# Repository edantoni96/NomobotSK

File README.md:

# NomobotSK

========== PCB DESIGN FOR NOMOBOT SK ==========

NomobotSK is a educational robot for kids to learn programming and robotics.

## TOP VIEW

## BOTTOM VIEW

## SCHEMATIC

[embed](https://github.com/edantoni96/NomobotSK/blob/main/docs/schematic.pdf)

## TESTER

To test the device you can use the under tester/TEST.ino

\***\*KONFIGURASI PIN\*\***

D1; Trig / Servo R
D2; Tombol 2
D3; Tombol 3
D4; DIR2 (-)
D5; DIR2 (+)
D6; DIR1 (-)
D7; DIR1 (+)
D8; LED / Garis L
D0; BUZZ / Garis R

Catatan: Simbol / berarti setiap fungsi perlu diuji atau digunakan secara terpisah.

\***\*Perintah PENGUJIAN\*\***

1. TEST_LED
2. TEST_BUZ
3. TEST_BUTTON
4. TEST_M1
5. TEST_M2
6. TEST_ULRA
7. TEST_LINE

\***\*Instruksi Uji\*\***

1. Buka Test.ino dengan Arduino.
2. compile Test.ino.
3. Hubungkan NodeMCU Anda ke komputer menggunakan kabel USB.
4. Pilih board dan port yang sesuai di Arduino IDE.
5. Unggah kode yang telah dikompilasi ke NodeMCU dengan mengklik tombol "Unggah".
6. Setelah pengunggahan selesai, buka Serial Monitor di Arduino IDE.
7. TEST_LED
   - Nyalakan pin LED
   - Ketik "TEST_LED" di Serial Monitor dan tekan Enter.
   - Pastikan bahwa LED yang terhubung ke pin D8 (Garis L) menyala.
8. TEST_BUZ
   - Nyalakan pin Buzz
   - Ketik "TEST_BUZ" di Serial Monitor dan tekan Enter.
   - Konfirmasikan bahwa buzzer yang terhubung ke pin D0 (Garis R) menghasilkan suara.
9. TEST_BUTTON
   - Nyalakan BTA dan BTB
   - Ketik "TEST_BUTTON" di Serial Monitor dan tekan Enter.
   - Tekan Tombol 2 (terhubung ke pin D2) dan Tombol 3 (terhubung ke pin D3) satu per satu.
   - Amati di Serial Monitor bahwa tekanan tombol yang sesuai terdeteksi.
10. TEST_M1
    - Nyalakan pin M1+ dan M1-
    - Ketik "TEST_M1" di Serial Monitor dan tekan Enter.
    - Pastikan bahwa motor (M1) merespons sesuai dengan sinyal DIR1 (-) dan DIR1 (+) pada pin D6 dan D7.
11. TEST_M2
    - Nyalakan pin M2+ dan M2-
    - Ketik "TEST_M2" di Serial Monitor dan tekan Enter.
    - Pastikan bahwa motor (M2) merespons sesuai dengan sinyal DIR2 (-) dan DIR2 (+) pada pin D4 dan D5.
12. TEST_ULRA
    - Nyalakan pin Echo dan Trig
    - Ketik "TEST_ULRA" di Serial Monitor dan tekan Enter.
    - Jika sensor ultrasonik terhubung, periksa Serial Monitor untuk pembacaan jarak.
13. TEST_LINE
    - Nyalakan pin Garis
    - Ketik "TEST_LINE" di Serial Monitor dan tekan Enter.
    - Amati perilaku sensor garis yang terhubung ke pin D8 (Garis L) dan D0 (Garis R).
    - Pastikan pembacaan sensor tercermin di Serial Monitor.

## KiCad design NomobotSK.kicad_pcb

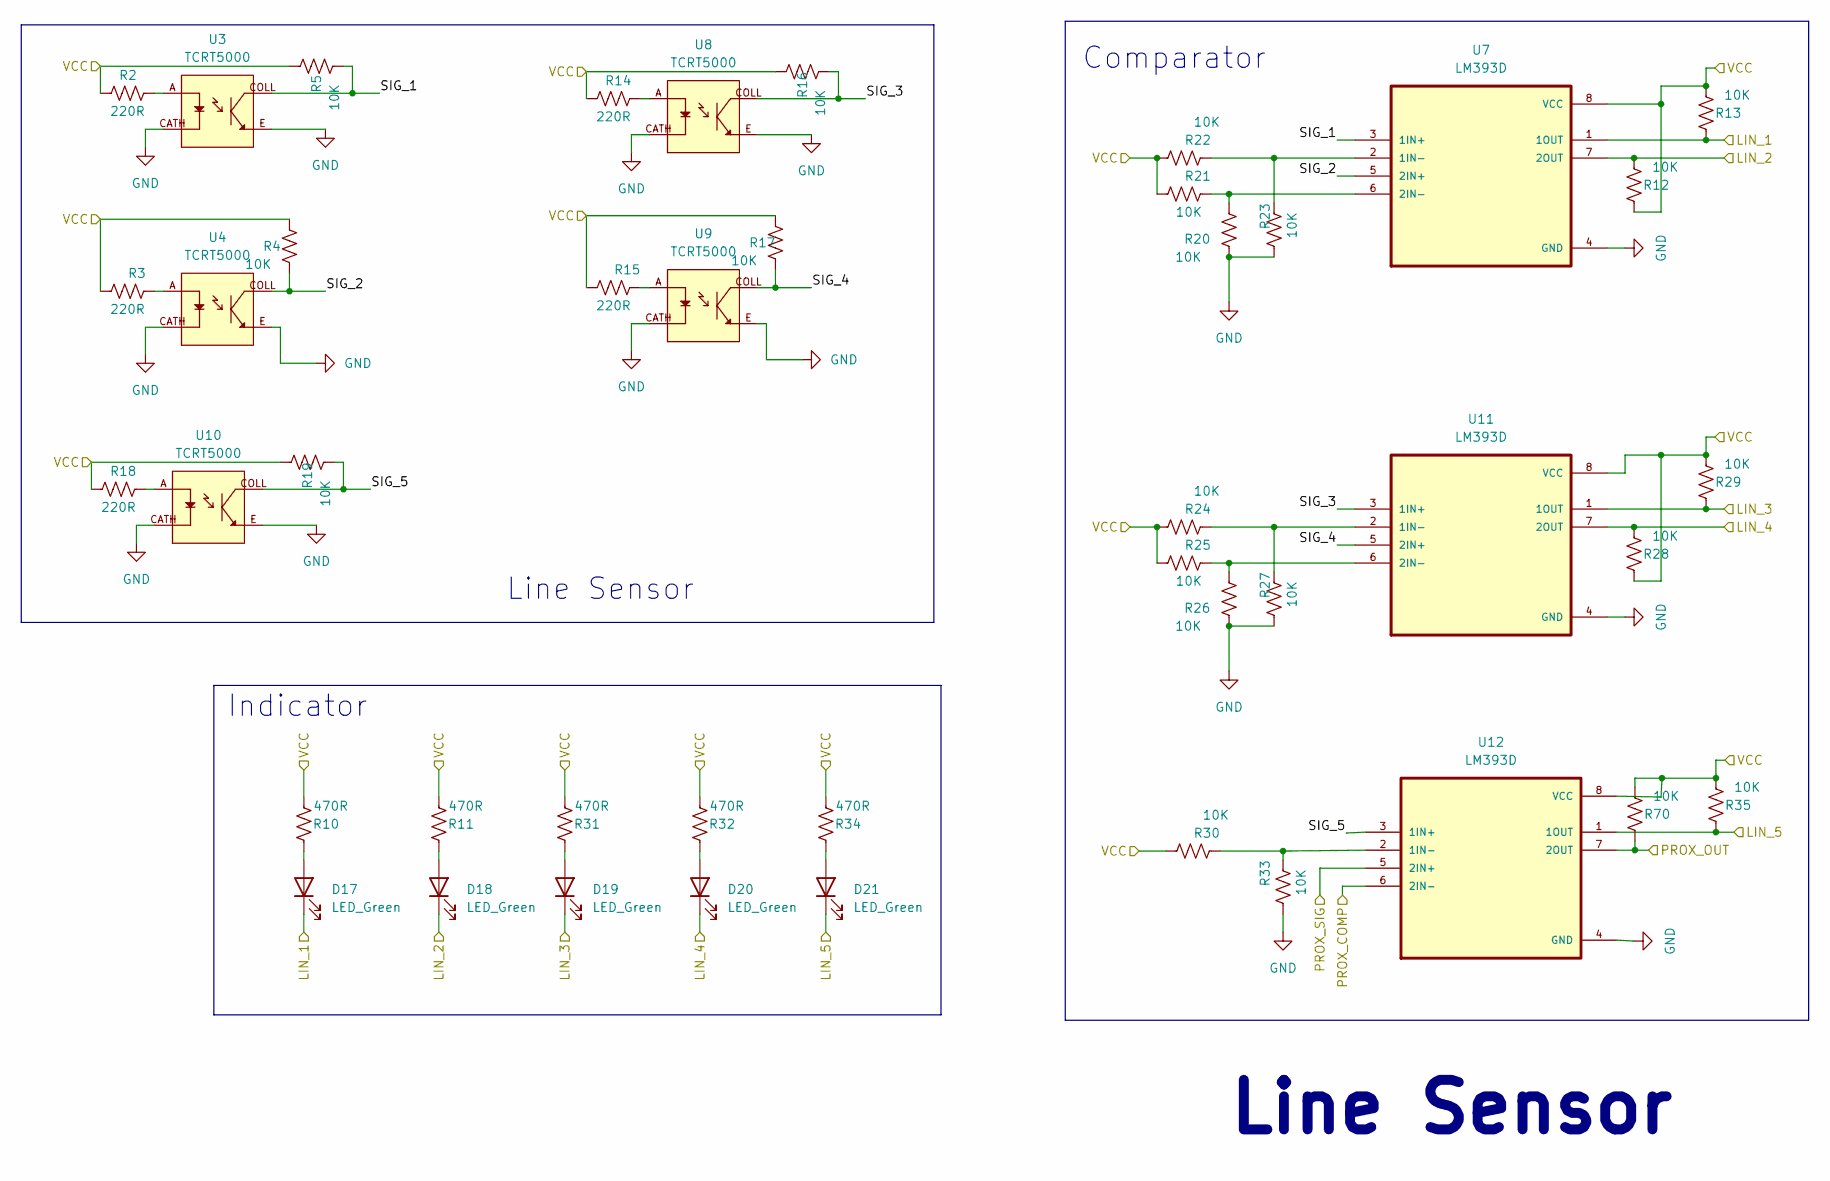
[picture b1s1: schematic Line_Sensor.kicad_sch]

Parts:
D17, D18, D19, D20, D21: LED_Green; LED_0805_2012Metric
R2, R3, R14, R15, R18: 220R; R_0805_2012Metric
R4, R5, R12, R13, R16, R17, R19, R20, R21, R22, R23, R24, R25, R26, R27, R28, R29, R30, R33, R35, R70: 10K; R_0805_2012Metric
R10, R11, R31, R32, R34: 470R; R_0805_2012Metric
U3, U4, U8, U9, U10: TCRT5000; OPTO_TCRT5000; PARTREV 1.7
U7, U11, U12: LM393D; SOIC127P599X175-8N

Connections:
/LINE SENSOR/LIN_1: D17.1 (K), R13.1, U7.1 (1OUT); also elsewhere on the board
/LINE SENSOR/LIN_2: D18.1 (K), R12.2, U7.7 (2OUT); also elsewhere on the board
/LINE SENSOR/LIN_3: D19.1 (K), R29.1, U11.1 (1OUT); also elsewhere on the board
/LINE SENSOR/LIN_4: D20.1 (K), R28.2, U11.7 (2OUT); also elsewhere on the board
/LINE SENSOR/LIN_5: D21.1 (K), R35.1, U12.1 (1OUT); also elsewhere on the board
/LINE SENSOR/PROX_COMP: U12.6 (2IN-); also elsewhere on the board
/LINE SENSOR/PROX_OUT: R70.1, U12.7 (2OUT); also elsewhere on the board
/LINE SENSOR/PROX_SIG: U12.5 (2IN+); also elsewhere on the board
/LINE SENSOR/SIG_1: R5.2, U3.COLL, U7.3 (1IN+)
/LINE SENSOR/SIG_2: R4.2, U4.COLL, U7.5 (2IN+)
/LINE SENSOR/SIG_3: R16.2, U8.COLL, U11.3 (1IN+)
/LINE SENSOR/SIG_4: R17.2, U9.COLL, U11.5 (2IN+)
/LINE SENSOR/SIG_5: R19.2, U10.COLL, U12.3 (1IN+)
/VDD: R2.2, R3.2, R4.1, R5.1, R10.2, R11.2, R12.1, R13.2, R14.2, R15.2, R16.1, R17.1, R18.2, R19.1, R21.2, R22.2, R24.2, R25.2, R28.1, R29.2, R30.2, R31.2, R32.2, R34.2, R35.2, R70.2, U7.8 (VCC), U11.8 (VCC), U12.8 (VCC); also elsewhere on the board
GND: R20.1, R23.2, R26.1, R27.2, R33.2, U3.CATH, U3.E, U4.CATH, U4.E, U7.4 (GND), U8.CATH, U8.E, U9.CATH, U9.E, U10.CATH, U10.E, U11.4 (GND), U12.4 (GND); also elsewhere on the board
unnamed: D17.2 (A), R10.1
unnamed: D18.2 (A), R11.1
unnamed: D19.2 (A), R31.1
unnamed: D20.2 (A), R32.1
unnamed: D21.2 (A), R34.1
unnamed: R2.1, U3.A
unnamed: R3.1, U4.A
unnamed: R14.1, U8.A
unnamed: R15.1, U9.A
unnamed: R18.1, U10.A
unnamed: R22.1, R23.1, U7.2 (1IN-)
unnamed: R20.2, R21.1, U7.6 (2IN-)
unnamed: R24.1, R27.1, U11.2 (1IN-)
unnamed: R25.1, R26.2, U11.6 (2IN-)
unnamed: R30.1, R33.1, U12.2 (1IN-)

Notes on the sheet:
Indicator
Line Sensor
Comparator

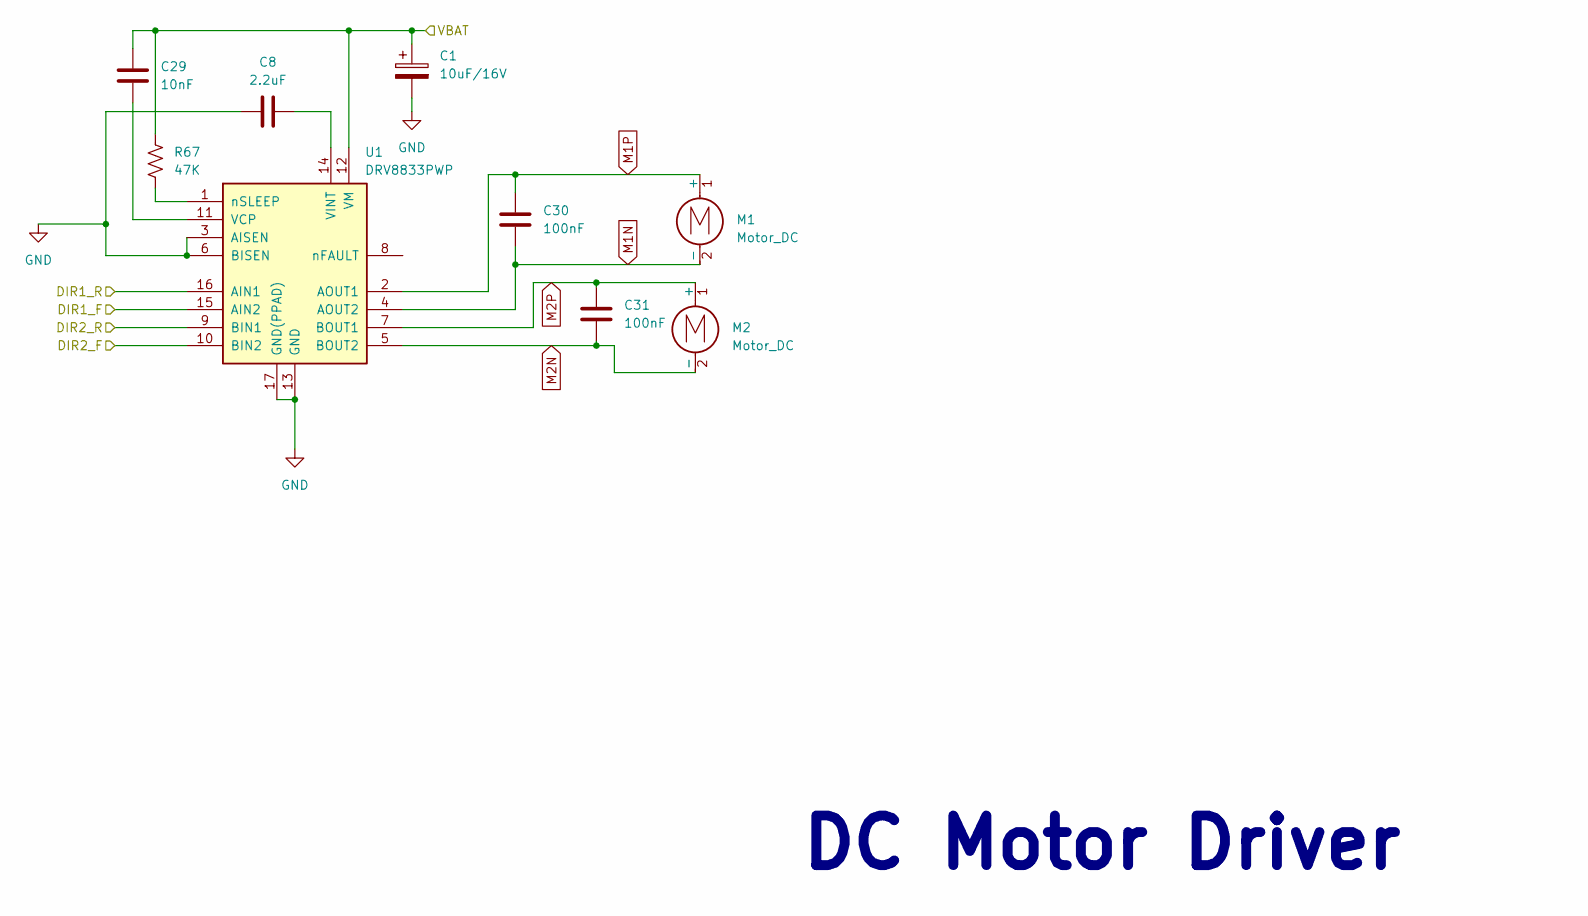
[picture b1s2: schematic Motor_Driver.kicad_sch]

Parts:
C1: 10uF/16V; C_Elec_4x5.4; Part RVT1C100M0405
C8: 2.2uF; C_0603_1608Metric
C29: 10nF; C_0603_1608Metric
C30, C31: 100nF; C_0603_1608Metric
M1, M2: Motor_DC; TerminalBlock_TE_282834-2_1x02_P2.54mm_Horizontal
R67: 47K; R_0603_1608Metric
U1: DRV8833PWP; HTSSOP-16-1EP_4.4x5mm_P0.65mm_EP3.4x5mm_Mask2.46x2.31mm_The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

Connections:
/MAIN MCU/IO16: U1.10 (BIN2); also elsewhere on the board
/MAIN MCU/IO17: U1.9 (BIN1); also elsewhere on the board
/MAIN MCU/IO18: U1.15 (AIN2); also elsewhere on the board
/MAIN MCU/IO19: U1.16 (AIN1); also elsewhere on the board
/POWER/VBAT: C1.1, C29.1, R67.2, U1.12 (VM); also elsewhere on the board
GND: C1.2, C8.2, U1.3 (AISEN), U1.6 (BISEN), U1.13 (GND), U1.17 (GND(PPAD)); also elsewhere on the board
M1N: C30.2, M1.2 (-), U1.4 (AOUT2)
M1P: C30.1, M1.1 (+), U1.2 (AOUT1)
M2N: C31.2, M2.2 (-), U1.5 (BOUT2)
M2P: C31.1, M2.1 (+), U1.7 (BOUT1)
unnamed: C29.2, U1.11 (VCP)
unnamed: C8.1, U1.14 (VINT)
unnamed: R67.1, U1.1 (nSLEEP)

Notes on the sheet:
DC Motor Driver

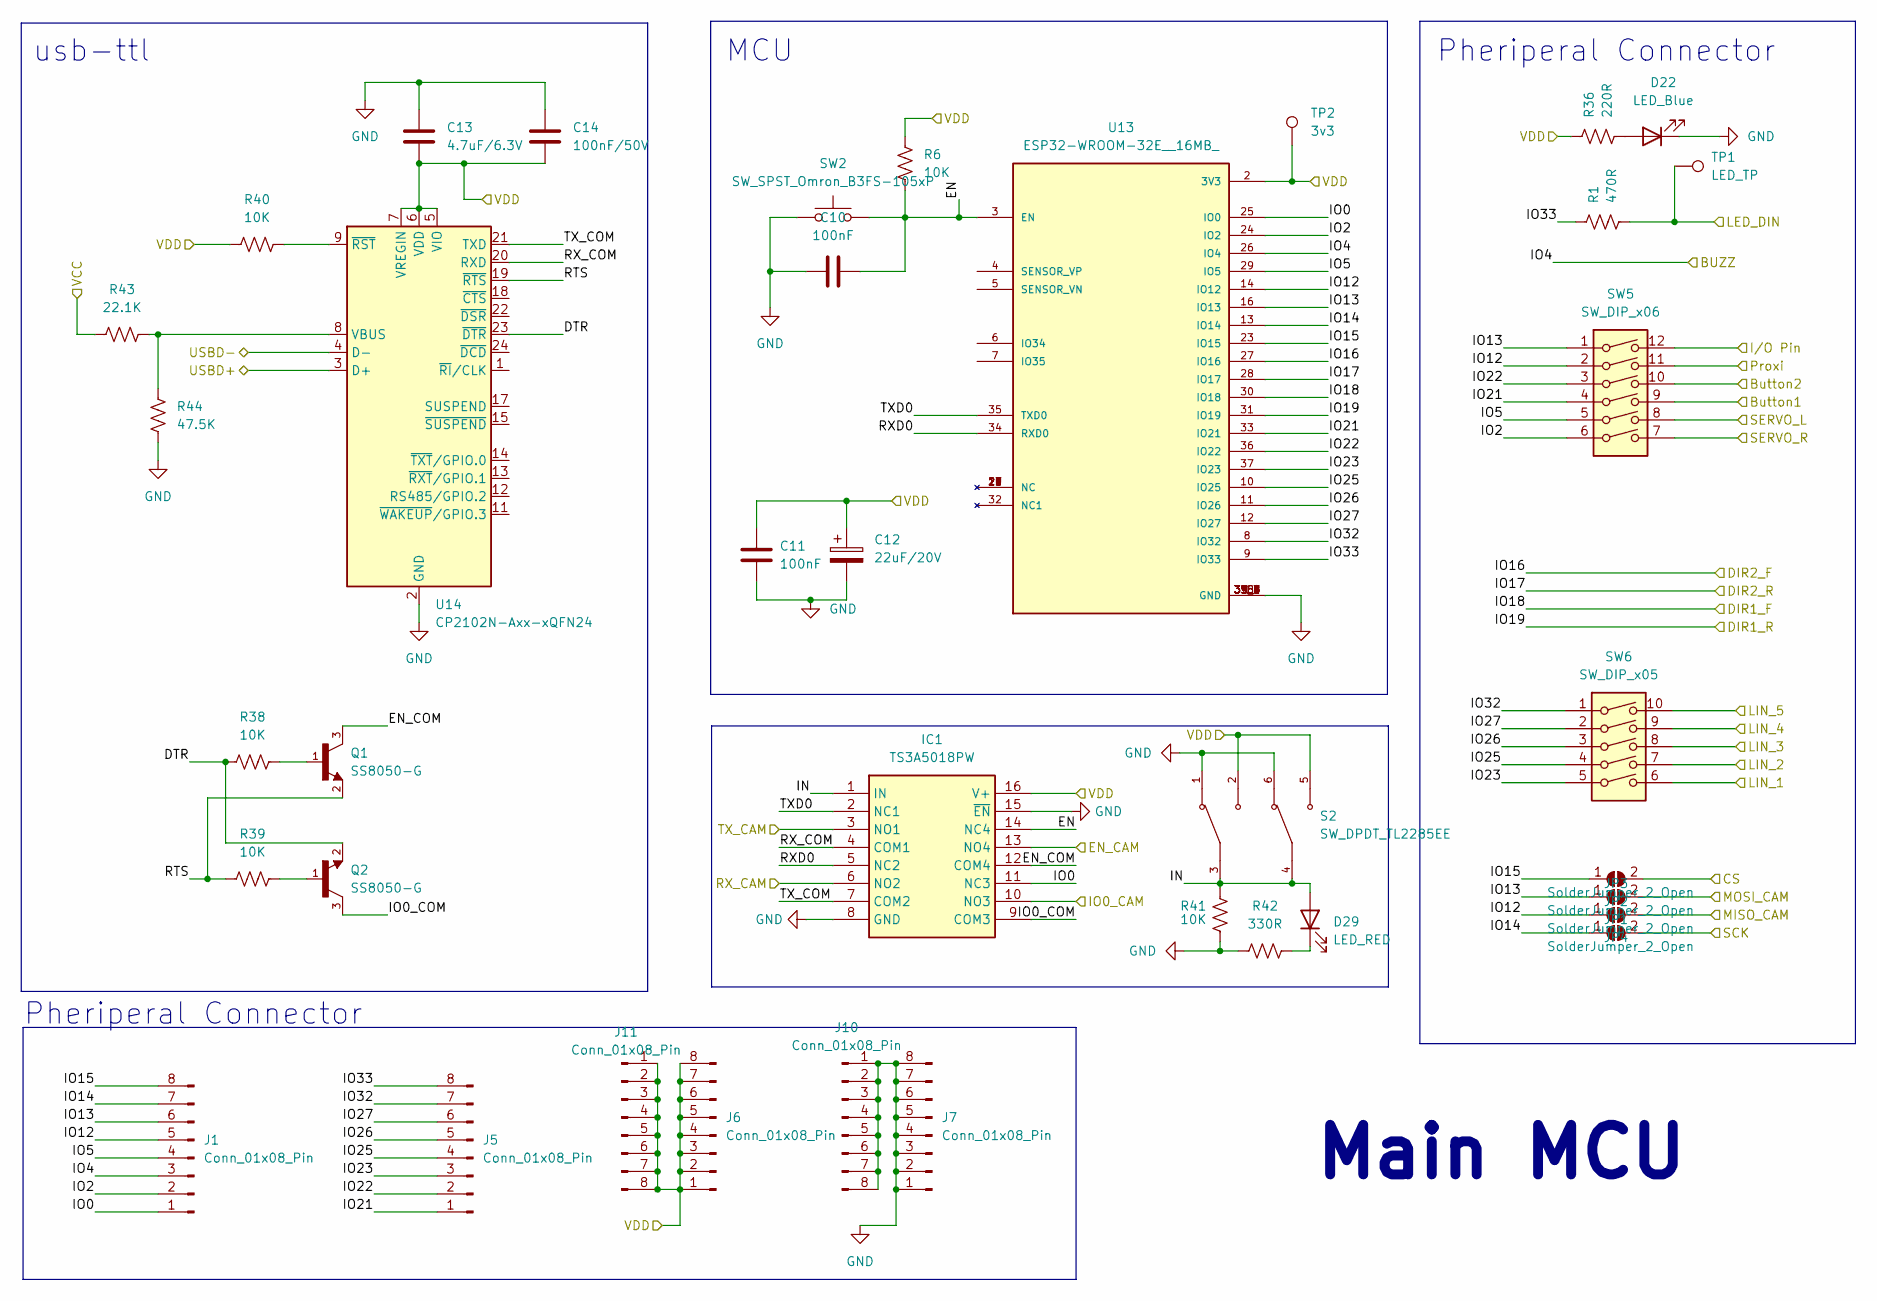
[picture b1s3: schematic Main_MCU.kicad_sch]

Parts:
C10, C11: 100nF; C_0603_1608Metric
C12: 22uF/20V; C_0805_2012Metric
C13: 4.7uF/6.3V; C_0603_1608Metric
C14: 100nF/50V; C_0603_1608Metric
D22: LED_Blue; LED_0805_2012Metric
D29: LED_RED; LED_0603_1608Metric
IC1: TS3A5018PW; SOP65P640X120-16N; Mouser Part Number 595-TS3A5018PW
J1, J5, J6, J7, J10, J11: Conn_01x08_Pin; PinHeader_1x08_P2.54mm_Vertical
JP1, JP2, JP3, JP4: SolderJumper_2_Open; SolderJumper-2_P1.3mm_Open_RoundedPad1.0x1.5mm
Q1, Q2: SS8050-G; TRANS_SS8050-G; PARTREV A
R1: 470R; R_0603_1608Metric
R6, R38, R39, R40, R41: 10K; R_0603_1608Metric
R36: 220R; R_0603_1608Metric
R42: 330R; R_0603_1608Metric
R43: 22.1K; R_0603_1608Metric
R44: 47.5K; R_0603_1608Metric
S2: SW_DPDT_TL2285EE; SW_TL2285EE; PARTREV B
SW2: SW_SPST_Omron_B3FS-105xP
SW5: SW_DIP_x06; SW_DIP_SPSTx06_Slide_9.78x17.42mm_W7.62mm_P2.54mm
SW6: SW_DIP_x05; SW_DIP_SPSTx05_Slide_9.78x14.88mm_W7.62mm_P2.54mm
TP1: LED_TP; TestPoint_Pad_D1.0mm
TP2: 3v3; TestPoint_Pad_D2.0mm
U13: ESP32-WROOM-32E__16MB_; XCVR_ESP32-WROOM-32E__16MB_; PARTREV 1.4
U14: CP2102N-Axx-xQFN24; QFN-24-1EP_4x4mm_P0.5mm_EP2.6x2.6mm_ThermalVias

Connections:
/CONNECTOR/D+: U14.3 (D+); also elsewhere on the board
/CONNECTOR/D-: U14.4 (D-); also elsewhere on the board
/LINE SENSOR/LIN_1: SW6.6; also elsewhere on the board
/LINE SENSOR/LIN_2: SW6.7; also elsewhere on the board
/LINE SENSOR/LIN_3: SW6.8; also elsewhere on the board
/LINE SENSOR/LIN_4: SW6.9; also elsewhere on the board
/LINE SENSOR/LIN_5: SW6.10; also elsewhere on the board
/LINE SENSOR/PROX_OUT: SW5.11; also elsewhere on the board
/MAIN MCU/Button1: SW5.9; also elsewhere on the board
/MAIN MCU/Button2: SW5.10; also elsewhere on the board
/MAIN MCU/CS: JP3.2 (B); also elsewhere on the board
/MAIN MCU/DTR: Q2.2, R38.1, U14.23 (~DTR)
/MAIN MCU/EN: C10.2, IC1.14 (NC4), R6.1, SW2.2, U13.3 (EN)
/MAIN MCU/EN_CAM: IC1.13 (NO4); also elsewhere on the board
/MAIN MCU/EN_COM: IC1.12 (COM4), Q1.3
/MAIN MCU/IN: D29.2 (A), IC1.1 (IN), R41.2, S2.3, S2.4
/MAIN MCU/IO0: IC1.11 (NC3), J1.1, U13.25 (IO0)
/MAIN MCU/IO0_CAM: IC1.10 (NO3); also elsewhere on the board
/MAIN MCU/IO0_COM: IC1.9 (COM3), Q2.3
/MAIN MCU/IO2: J1.2, SW5.6, U13.24 (IO2)
/MAIN MCU/IO4: J1.3, U13.26 (IO4); also elsewhere on the board
/MAIN MCU/IO5: J1.4, SW5.5, U13.29 (IO5)
/MAIN MCU/IO12: J1.5, JP1.1 (A), SW5.2, U13.14 (IO12)
/MAIN MCU/IO13: J1.6, JP2.1 (A), SW5.1, U13.16 (IO13)
/MAIN MCU/IO14: J1.7, JP4.1 (A), U13.13 (IO14)
/MAIN MCU/IO15: J1.8, JP3.1 (A), U13.23 (IO15)
/MAIN MCU/IO16: U13.27 (IO16); also elsewhere on the board
/MAIN MCU/IO17: U13.28 (IO17); also elsewhere on the board
/MAIN MCU/IO18: U13.30 (IO18); also elsewhere on the board
/MAIN MCU/IO19: U13.31 (IO19); also elsewhere on the board
/MAIN MCU/IO21: J5.1, SW5.4, U13.33 (IO21)
/MAIN MCU/IO22: J5.2, SW5.3, U13.36 (IO22)
/MAIN MCU/IO23: J5.3, SW6.5, U13.37 (IO23)
/MAIN MCU/IO25: J5.4, SW6.4, U13.10 (IO25)
/MAIN MCU/IO26: J5.5, SW6.3, U13.11 (IO26)
/MAIN MCU/IO27: J5.6, SW6.2, U13.12 (IO27)
/MAIN MCU/IO32: J5.7, SW6.1, U13.8 (IO32)
/MAIN MCU/IO33: J5.8, R1.1, U13.9 (IO33)
/MAIN MCU/I/O Pin: SW5.12; also elsewhere on the board
/MAIN MCU/LED_DIN: R1.2, TP1.1; also elsewhere on the board
/MAIN MCU/MISO_CAM: JP1.2 (B); also elsewhere on the board
/MAIN MCU/MOSI_CAM: JP2.2 (B); also elsewhere on the board
/MAIN MCU/RTS: Q1.2, R39.2, U14.19 (~RTS)
/MAIN MCU/RXD0: IC1.5 (NC2), U13.34 (RXD0)
/MAIN MCU/RX_CAM: IC1.6 (NO2); also elsewhere on the board
/MAIN MCU/RX_COM: IC1.4 (COM1), U14.20 (RXD)
/MAIN MCU/SCK: JP4.2 (B); also elsewhere on the board
/MAIN MCU/SERVO_L: SW5.8; also elsewhere on the board
/MAIN MCU/SERVO_R: SW5.7; also elsewhere on the board
/MAIN MCU/TXD0: IC1.2 (NC1), U13.35 (TXD0)
/MAIN MCU/TX_CAM: IC1.3 (NO1); also elsewhere on the board
/MAIN MCU/TX_COM: IC1.7 (COM2), U14.21 (TXD)
/VCC: R43.2; also elsewhere on the board
/VDD: C11.1, C12.1, C13.1, C14.1, IC1.16 (V+), J6.1, J6.2, J6.3, J6.4, J6.5, J6.6, J6.7, J6.8, J11.1, J11.2, J11.3, J11.4, J11.5, J11.6, J11.7, J11.8, R6.2, R36.1, R40.2, S2.2, S2.5, TP2.1, U13.2 (3V3), U14.5 (VIO), U14.6 (VDD), U14.7 (VREGIN); also elsewhere on the board
GND: C10.1, C11.2, C12.2, C13.2, C14.2, D22.1 (K), IC1.8 (GND), IC1.15 (~EN), J7.1, J7.2, J7.3, J7.4, J7.5, J7.6, J7.7, J7.8, J10.1, J10.2, J10.3, J10.4, J10.5, J10.6, J10.7, J10.8, R41.1, R42.2, R44.2, S2.1, S2.6, SW2.1, U13.1 (GND), U13.15 (GND), U13.38 (GND), U13.39_1 (GND), U13.39_2 (GND), U13.39_3 (GND), U13.39_4 (GND), U13.39_5 (GND), U13.39_6 (GND), U13.39_7 (GND), U13.39_8 (GND), U13.39_9 (GND), U13.39_10 (GND), U13.39_11 (GND), U13.39_12 (GND), U13.39_13 (GND), U13.39_14 (GND), U13.39_15 (GND), U13.39_16 (GND), U13.39_17 (GND), U13.39_18 (GND), U13.39_19 (GND), U13.39_20 (GND), U13.39_21 (GND), U14.2 (GND), U14.25 (GND); also elsewhere on the board
unnamed: D22.2 (A), R36.2
unnamed: D29.1 (K), R42.1
unnamed: Q1.1, R38.2
unnamed: Q2.1, R39.1
unnamed: R43.1, R44.1, U14.8 (VBUS)
unnamed: R40.1, U14.9 (~RST)

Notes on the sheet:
Pheriperal Connector
usb-ttl
Main MCU
MCU

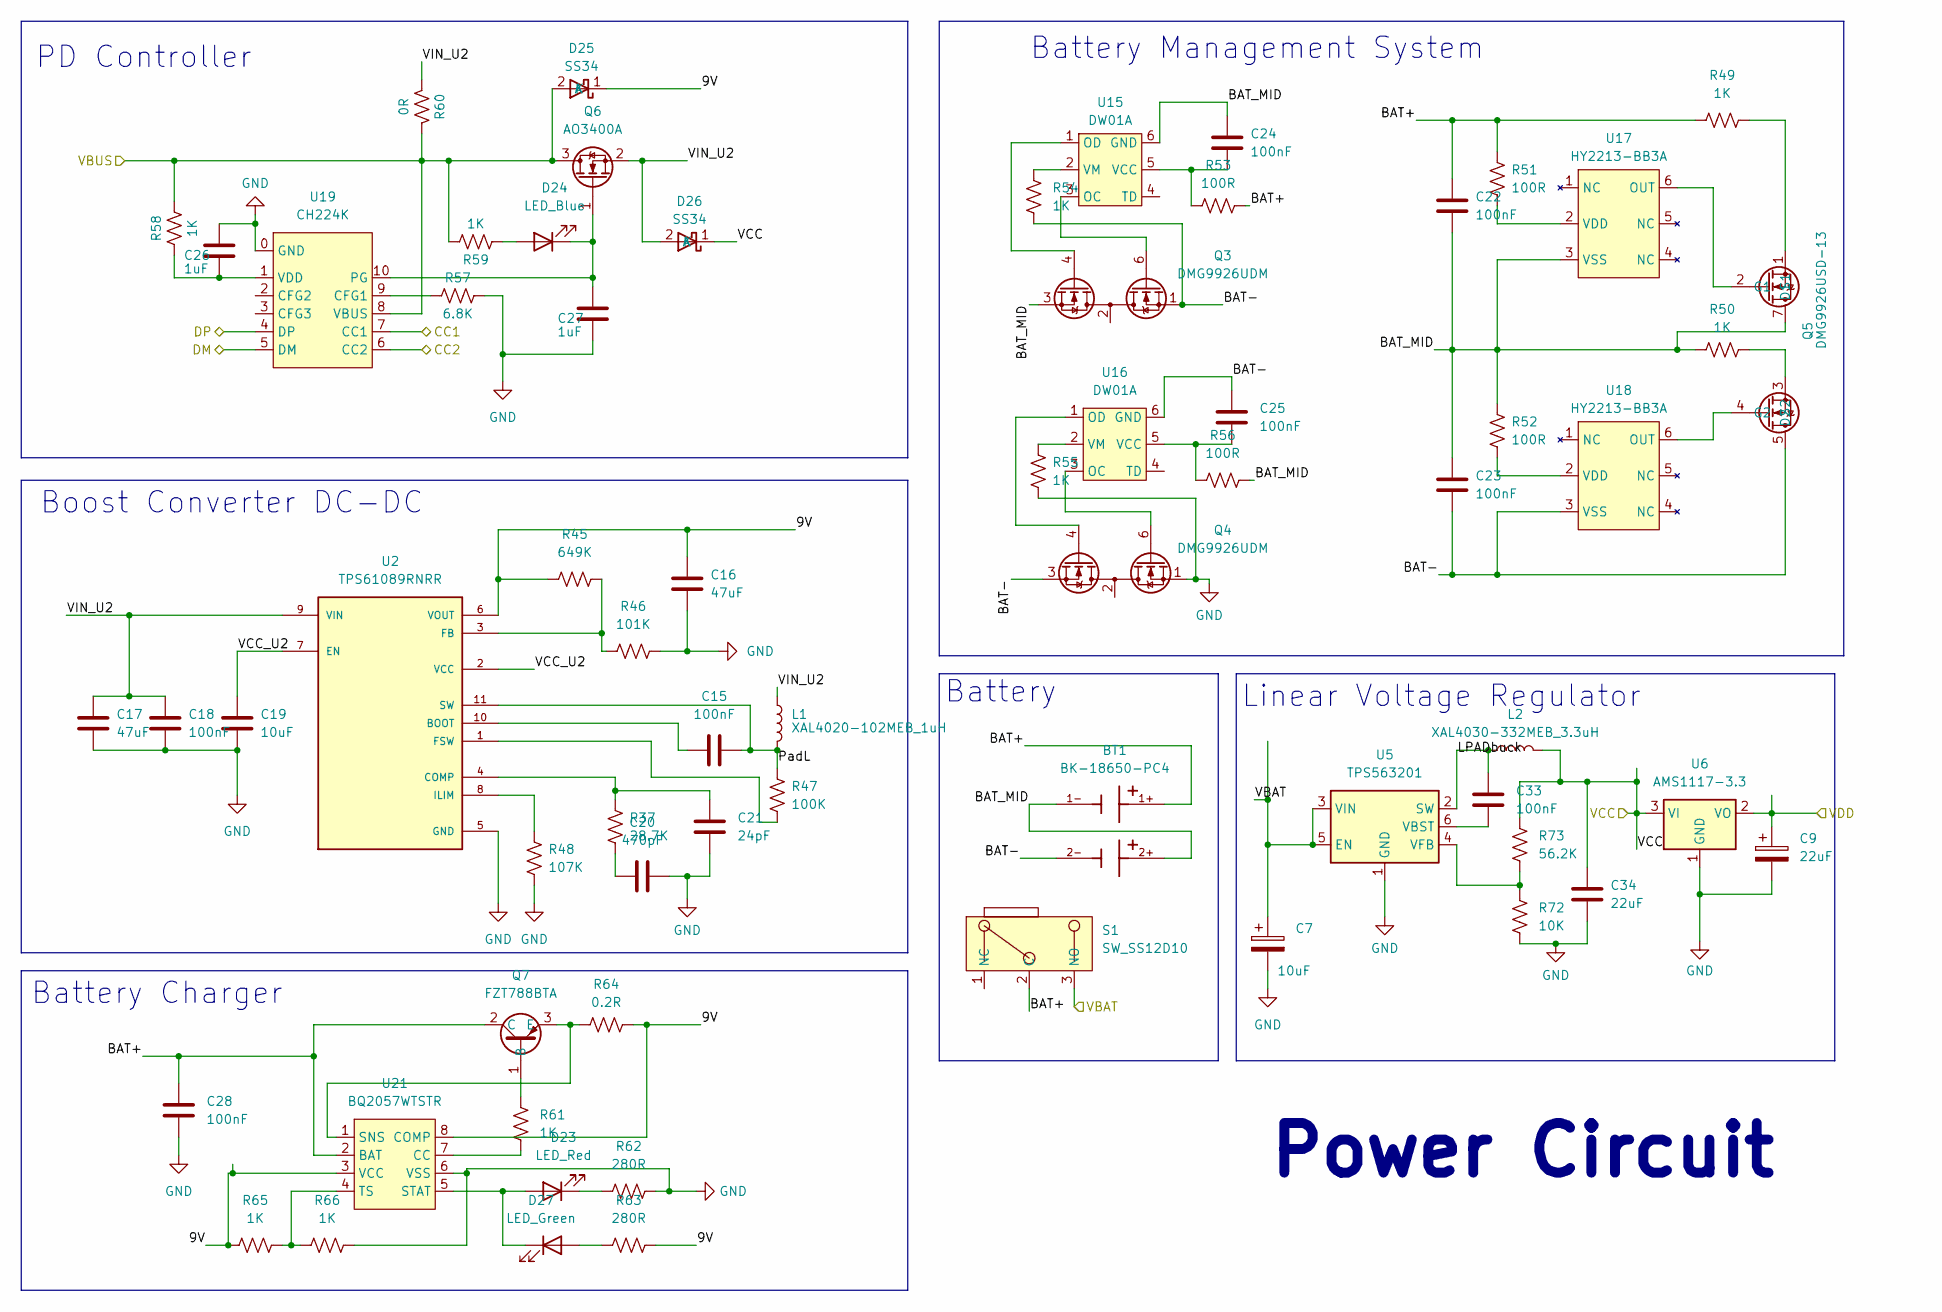
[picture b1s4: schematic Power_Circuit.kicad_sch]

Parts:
BT1: BK-18650-PC4; BAT_BK-18650-PC4; PARTREV K
C7: 10uF; CP_Elec_6.3x5.3
C9: 22uF; CP_Elec_6.3x5.3
C15, C18, C22, C23, C24, C25, C28, C33: 100nF; C_0402_1005Metric
C16, C17: 47uF; C_1206_3216Metric
C19: 10uF; C_0603_1608Metric
C20: 470pF; C_0805_2012Metric
C21: 24pF; C_0402_1005Metric
C26, C27: 1uF; C_1206_3216Metric
C34: 22uF; C_0603_1608Metric
D23: LED_Red; LED_0805_2012Metric
D24: LED_Blue; LED_0805_2012Metric
D25, D26: SS34; D_SMA_Handsoldering
D27: LED_Green; LED_0805_2012Metric
L1: XAL4020-102MEB_1uH; L_Coilcraft_XAL4020-XXX
L2: XAL4030-332MEB_3.3uH; L_Coilcraft_XAL4030-XXX
Q3, Q4: DMG9926UDM; SOT-23-6
Q5: DMG9926USD-13; SO-8_5.3x6.2mm_P1.27mm
Q6: AO3400A; SOT-23
Q7: FZT788BTA; SOT-223-3_TabPin2
R37: 28.7K; R_0603_1608Metric
R45: 649K; C_0603_1608Metric
R46: 101K; C_0603_1608Metric
R47: 100K; R_0603_1608Metric
R48: 107K; R_0603_1608Metric
R49, R50: 1K; R_1206_3216Metric
R51, R52, R53, R56: 100R; C_0603_1608Metric
R54, R55, R58, R59, R61, R65, R66: 1K; C_0603_1608Metric
R57: 6.8K; C_0603_1608Metric
R60: 0R; C_0805_2012Metric
R62, R63: 280R; R_0603_1608Metric
R64: 0.2R; R_0603_1608Metric
R72: 10K; C_0603_1608Metric
R73: 56.2K; C_0603_1608Metric
S1: SW_SS12D10; SW_SS-12D10-G5050
U2: TPS61089RNRR; IC_TPS61089RNRR; PARTREV B
U5: TPS563201; SOT-23-6
U6: AMS1117-3.3; SOT-223-3_TabPin2
U15, U16: DW01A; SOT-23-6
U17, U18: HY2213-BB3A; SOT-23-6
U19: CH224K; ESSOP-10
U21: BQ2057WTSTR; TSSOP-8_4.4x3mm_P0.65mm

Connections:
/CONNECTOR/CC1: U19.7 (CC1); also elsewhere on the board
/CONNECTOR/CC2: U19.6 (CC2); also elsewhere on the board
/CONNECTOR/D+: U19.4 (DP); also elsewhere on the board
/CONNECTOR/D-: U19.5 (DM); also elsewhere on the board
/CONNECTOR/VBUS: D25.2 (A), Q6.3 (D), R58.2, R59.2, R60.1, U19.8 (VBUS); also elsewhere on the board
/POWER/9V: C16.1, D25.1 (K), R45.1, R63.1, R64.2, R65.1, U2.6 (VOUT), U21.3 (VCC), U21.8 (COMP)
/POWER/BAT+: BT1.1+, C22.2, C28.2, Q7.2 (C), R49.1, R51.2, R53.1, S1.2 (C), U21.2 (BAT)
/POWER/BAT-: BT1.2-, C23.1, C25.1, Q3.1 (D1), Q4.3 (S2), Q5.5 (D2), Q5.6 (D2), R54.2, U16.6 (GND), U18.3 (VSS)
/POWER/BAT_MID: BT1.1-, BT1.2+, C22.1, C23.2, C24.1, Q3.3 (S2), Q5.7 (D1), Q5.8 (D1), R50.1, R52.2, R56.1, U15.6 (GND), U17.3 (VSS)
/POWER/LPADbuck: C33.1, L2.1, U5.2 (SW)
/POWER/PadL: C15.2, L1.2, R47.2, U2.11 (SW), U2.12 (SW)
/POWER/VBAT: C7.1, S1.3 (NO), U5.3 (VIN), U5.5 (EN); also elsewhere on the board
/POWER/VCC_U2: C19.2, U2.2 (VCC), U2.7 (EN)
/POWER/VIN_U2: C17.2, C18.2, D26.2 (A), L1.1, Q6.2 (S), R60.2, U2.9 (VIN)
/VCC: C34.2, D26.1 (K), L2.2, R73.2, U6.3 (VI); also elsewhere on the board
/VDD: C9.1, U6.2 (VO); also elsewhere on the board
GND: C7.2, C9.2, C16.2, C17.1, C18.1, C19.1, C20.1, C21.1, C26.2, C27.1, C28.1, C34.1, Q4.1 (D1), R46.2, R48.1, R55.2, R57.2, R62.1, R66.2, R72.1, U2.5 (GND), U5.1 (GND), U6.1 (GND), U19.0 (GND), U21.6 (VSS); also elsewhere on the board
unnamed: C20.2, R37.2
unnamed: D23.2 (A), D27.1 (K), U21.5 (STAT)
unnamed: D23.1 (K), R62.2
unnamed: D24.2 (A), R59.1
unnamed: C27.2, D24.1 (K), Q6.1 (G), U19.10 (PG)
unnamed: D27.2 (A), R63.2
unnamed: Q3.6 (G1), U15.3 (OC)
unnamed: Q3.4 (G2), U15.1 (OD)
unnamed: Q3.2 (S1/D2), Q3.5 (S1/D2)
unnamed: Q4.6 (G1), U16.3 (OC)
unnamed: Q4.4 (G2), U16.1 (OD)
unnamed: Q4.2 (S1/D2), Q4.5 (S1/D2)
unnamed: Q5.2 (G1), U17.6 (OUT)
unnamed: Q5.4 (G2), U18.6 (OUT)
unnamed: Q5.1 (S1), R49.2
unnamed: Q5.3 (S2), R50.2
unnamed: Q7.1 (B), R61.1
unnamed: Q7.3 (E), R64.1, U21.1 (SNS)
unnamed: C15.1, U2.10 (BOOT)
unnamed: C21.2, R37.1, U2.4 (COMP)
unnamed: R45.2, R46.1, U2.3 (FB)
unnamed: R47.1, U2.1 (FSW)
unnamed: R48.2, U2.8 (ILIM)
unnamed: C33.2, U5.6 (VBST)
unnamed: R72.2, R73.1, U5.4 (VFB)
unnamed: C24.2, R53.2, U15.5 (VCC)
unnamed: R54.1, U15.2 (VM)
unnamed: C25.2, R56.2, U16.5 (VCC)
unnamed: R55.1, U16.2 (VM)
unnamed: R51.1, U17.2 (VDD)
unnamed: R52.1, U18.2 (VDD)
unnamed: R57.1, U19.9 (CFG1)
unnamed: C26.1, R58.1, U19.1 (VDD)
unnamed: R61.2, U21.7 (CC)
unnamed: R65.2, R66.1, U21.4 (TS)

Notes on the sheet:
Battery Charger
Battery
Linear Voltage Regulator
Boost Converter DC-DC
Battery Management System
Power Circuit
PD Controller

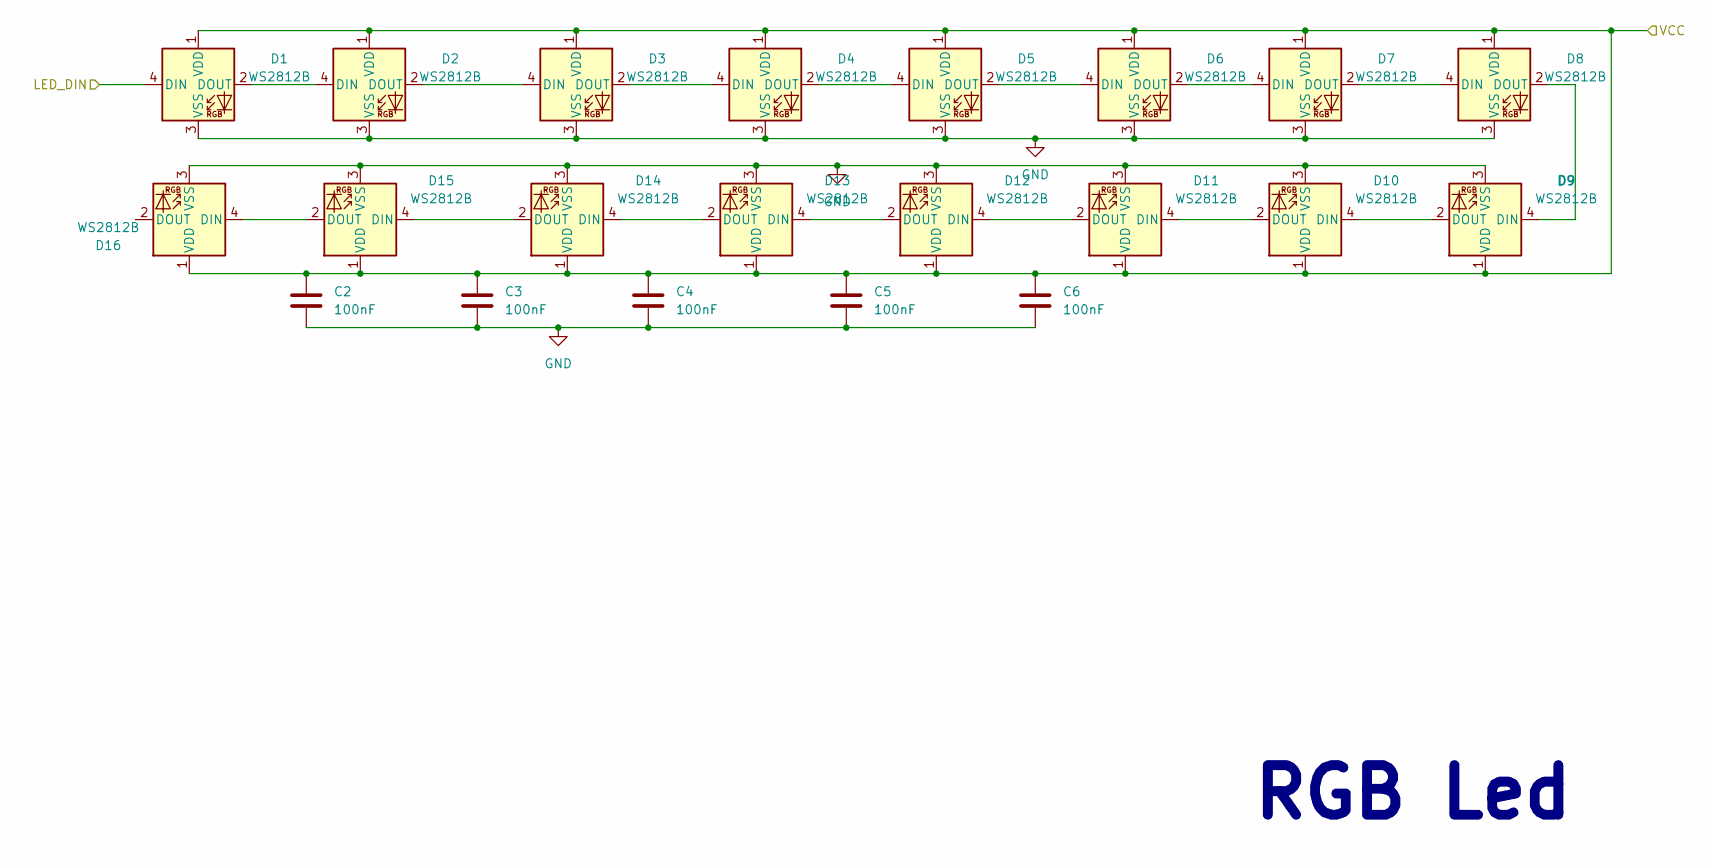
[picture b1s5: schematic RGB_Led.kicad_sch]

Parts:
C2, C3, C4, C5, C6: 100nF; C_0805_2012Metric
D1, D2, D3, D4, D5, D6, D7, D8, D9, D10, D11, D12, D13, D14, D15, D16: WS2812B; LED_WS2812B_PLCC4_5.0x5.0mm_P3.2mm

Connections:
/MAIN MCU/LED_DIN: D1.4 (DIN); also elsewhere on the board
/VCC: C2.1, C3.1, C4.1, C5.1, C6.1, D1.1 (VDD), D2.1 (VDD), D3.1 (VDD), D4.1 (VDD), D5.1 (VDD), D6.1 (VDD), D7.1 (VDD), D8.1 (VDD), D9.1 (VDD), D10.1 (VDD), D11.1 (VDD), D12.1 (VDD), D13.1 (VDD), D14.1 (VDD), D15.1 (VDD), D16.1 (VDD); also elsewhere on the board
GND: C2.2, C3.2, C4.2, C5.2, C6.2, D1.3 (VSS), D2.3 (VSS), D3.3 (VSS), D4.3 (VSS), D5.3 (VSS), D6.3 (VSS), D7.3 (VSS), D8.3 (VSS), D9.3 (VSS), D10.3 (VSS), D11.3 (VSS), D12.3 (VSS), D13.3 (VSS), D14.3 (VSS), D15.3 (VSS), D16.3 (VSS); also elsewhere on the board
unnamed: D1.2 (DOUT), D2.4 (DIN)
unnamed: D2.2 (DOUT), D3.4 (DIN)
unnamed: D3.2 (DOUT), D4.4 (DIN)
unnamed: D4.2 (DOUT), D5.4 (DIN)
unnamed: D5.2 (DOUT), D6.4 (DIN)
unnamed: D6.2 (DOUT), D7.4 (DIN)
unnamed: D7.2 (DOUT), D8.4 (DIN)
unnamed: D8.2 (DOUT), D9.4 (DIN)
unnamed: D9.2 (DOUT), D10.4 (DIN)
unnamed: D10.2 (DOUT), D11.4 (DIN)
unnamed: D11.2 (DOUT), D12.4 (DIN)
unnamed: D12.2 (DOUT), D13.4 (DIN)
unnamed: D13.2 (DOUT), D14.4 (DIN)
unnamed: D14.2 (DOUT), D15.4 (DIN)
unnamed: D15.2 (DOUT), D16.4 (DIN)

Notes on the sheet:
RGB Led

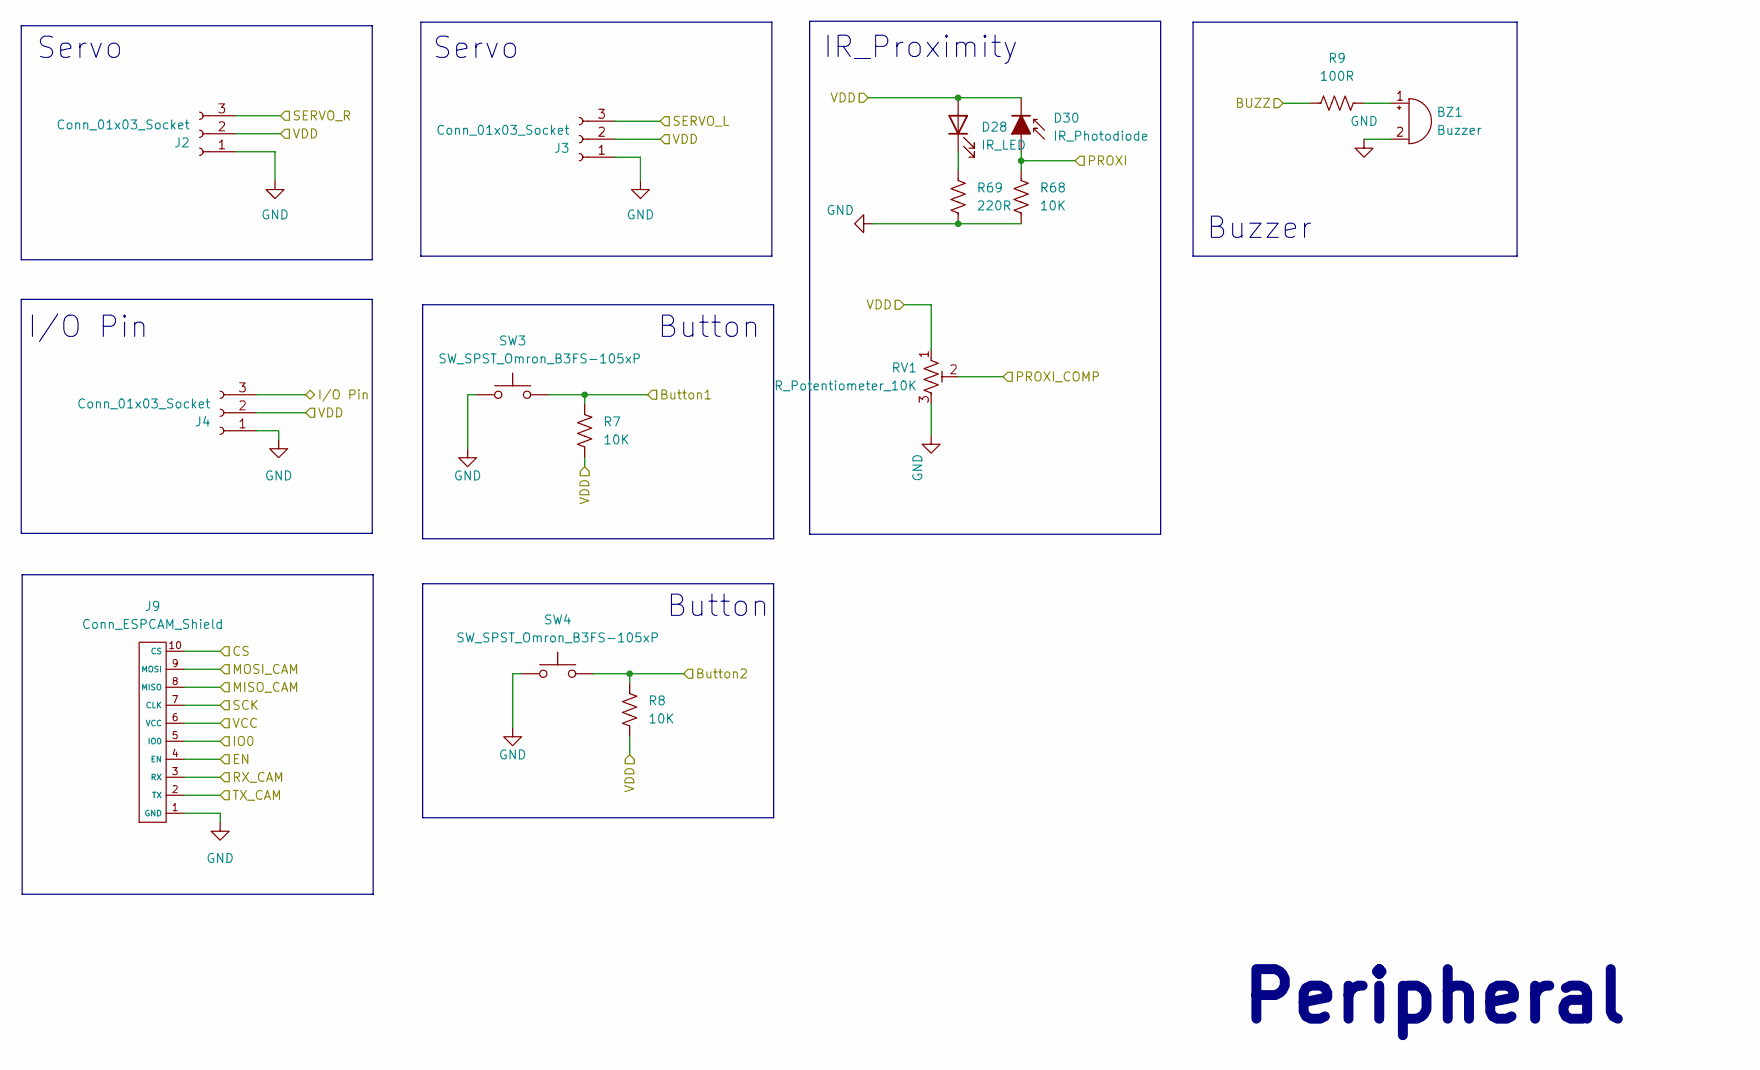
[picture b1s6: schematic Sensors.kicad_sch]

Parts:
BZ1: Buzzer; Buzzer_12x9.5RM7.6
D28: IR_LED; LED_D5.0mm_Horizontal_O1.27mm_Z3.0mm_IRBlack
D30: IR_Photodiode; LED_D5.0mm_Horizontal_O1.27mm_Z3.0mm_Clear
J2, J3, J4: Conn_01x03_Socket; JST_EH_B3B-EH-A_1x03_P2.50mm_Vertical
J9: Conn_ESPCAM_Shield; Conn_ESPCAM_Shield-Female
R7, R8, R68: 10K; R_0805_2012Metric
R9: 100R; R_0805_2012Metric
R69: 220R; R_0805_2012Metric
RV1: R_Potentiometer_10K; Potentiometer_Bourns_3296W_Vertical
SW3, SW4: SW_SPST_Omron_B3FS-105xP

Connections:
/LINE SENSOR/PROX_COMP: RV1.2; also elsewhere on the board
/LINE SENSOR/PROX_SIG: D30.2 (A), R68.1; also elsewhere on the board
/MAIN MCU/Button1: R7.1, SW3.2; also elsewhere on the board
/MAIN MCU/Button2: R8.1, SW4.2; also elsewhere on the board
/MAIN MCU/CS: J9.10 (CS); also elsewhere on the board
/MAIN MCU/EN_CAM: J9.4 (EN); also elsewhere on the board
/MAIN MCU/IO0_CAM: J9.5 (IO0); also elsewhere on the board
/MAIN MCU/IO4: R9.1; also elsewhere on the board
/MAIN MCU/I/O Pin: J4.3; also elsewhere on the board
/MAIN MCU/MISO_CAM: J9.9 (MOSI); also elsewhere on the board
/MAIN MCU/MOSI_CAM: J9.8 (MISO); also elsewhere on the board
/MAIN MCU/RX_CAM: J9.3 (RX); also elsewhere on the board
/MAIN MCU/SCK: J9.7 (CLK); also elsewhere on the board
/MAIN MCU/SERVO_L: J3.3; also elsewhere on the board
/MAIN MCU/SERVO_R: J2.3; also elsewhere on the board
/MAIN MCU/TX_CAM: J9.2 (TX); also elsewhere on the board
/VCC: J9.6 (VCC); also elsewhere on the board
/VDD: D28.2 (A), D30.1 (K), J2.2, J3.2, J4.2, R7.2, R8.2, RV1.1; also elsewhere on the board
GND: BZ1.2 (+), J2.1, J3.1, J4.1, J9.1 (GND), J9.11 (GND), R68.2, R69.2, RV1.3, SW3.1, SW4.1; also elsewhere on the board
unnamed: BZ1.1 (-), R9.2
unnamed: D28.1 (K), R69.1

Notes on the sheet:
Button
Servo
I/O Pin
Peripheral
Buzzer
IR_Proximity
